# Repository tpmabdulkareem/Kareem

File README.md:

##                                          Welcome to Kareem's Fablab 
<br> 

### "_Make Almost Anything!, a brilliant creative space for budding product designers and entrepreneurs to test out their ideas and bring them to life._"

### What is fablab?

   _Fab labs provide widespread access to modern means for invention. They began as an outreach project from MIT's Center for Bits and    Atoms (CBA), and became into a collaborative and global network. You can find more information about Fab Labs on the Fab Foundation   Website. The annotated photo below illustrates the facilities of a typical Fab Lab._
   
   _A fab lab (fabrication laboratory) is a small-scale workshop offering (personal) digital fabrication. A fab lab is typically equipped with an array of flexible computer-controlled tools that cover several different length scales and various materials, with the aim to make "almost anything". This includes technology-enabled products generally perceived as limited to mass production._
   
  _While fab labs have yet to compete with mass production and its associated economies of scale in fabricating widely distributed products, they have already shown the potential to empower individuals to create smart devices for themselves. These devices can be tailored to local or personal needs in ways that are not practical or economical using mass production._
   
   _The fab lab movement is closely aligned with the DIY, the open source hardware and the free and open source movement, and shares philosophy as well as technology with them._
   
   ----

#  [ABOUT ME](https://tpmabdulkareem.github.io/About)  (Click here) 
   
-----

# _Course Progress_

##   _SYLLABUS & CONTENTS_

  Day 1 : [Introduction To Fablab](https://tpmabdulkareem.github.io/Day1)

  Day 2 : [Github Pages and Documentation](https://tpmabdulkareem.github.io/Day2)
                               
  Day 3 : [Laser Cutting,Moulding and Casting](https://tpmabdulkareem.github.io/Day3)
                                
  Day 4 : [Vinyl Cutting](https://tpmabdulkareem.github.io/Day4)
                                	
  Day 5 : [Screen Printing](https://tpmabdulkareem.github.io/Day5)
                                	
  Day 6 : [3D Printing](https://tpmabdulkareem.github.io/Day6)
                                
  Day 7 : [Electronics Production and CNC](https://tpmabdulkareem.github.io/Day7)
  
  ----
                                
##   [Projects](https://tpmabdulkareem.github.io/project)
 
 -----

## [Gallery](https://tpmabdulkareem.github.io/gallery)

 -----

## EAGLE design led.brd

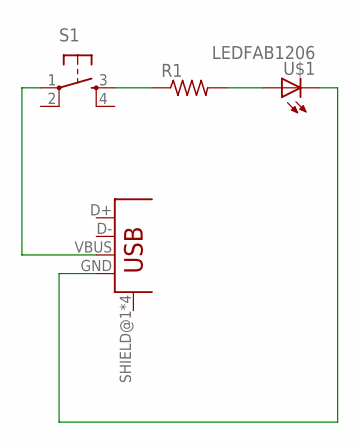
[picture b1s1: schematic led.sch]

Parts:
R1: RES-US1206FAB; R1206FAB
S1: 6MM_SWITCH6MM_SWITCH; 6MM_SWITCH
U$1: LEDFAB1206; LED1206FAB
U$2: USB_MINIB

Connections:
unnamed: S1.1, U$2.VBUS
unnamed: R1.1, S1.3 (S)
unnamed: R1.2, U$1.1 (A)
unnamed: U$1.2 (C), U$2.GND

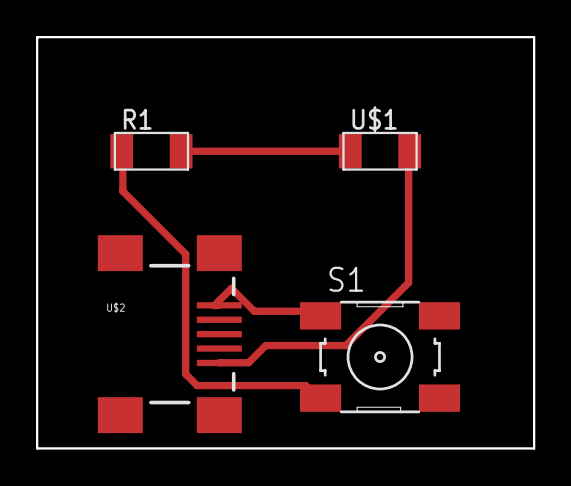
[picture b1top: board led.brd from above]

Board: 2 copper layers, 27.6 x 22.9 mm, 4 parts (0 on the bottom side), 4 nets.

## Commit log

2017-08-23 Set theme jekyll-theme-midnight
2017-08-24 Create About me
2017-08-24 Set theme jekyll-theme-hacker
2017-08-24 Rename About me.md to About.md
2017-08-24 Create DAY1
2017-09-03 Set theme jekyll-theme-leap-day
2017-09-03 Set theme jekyll-theme-dinky
2017-09-03 Set theme jekyll-theme-slate
2017-09-03 Create day2
2017-09-03 Rename DAY1 to Day1
2017-09-03 Rename day2 to Day2
2017-09-03 Create gallery
2017-09-03 Rename Day1 to Day1.md
2017-09-05 Set theme jekyll-theme-cayman
2017-09-06 Create Day6
2017-09-06 Update Day6
2017-09-06 Rename Day6 to Day6.md
2017-09-07 Create 3D
2017-09-07 Rename 3D to 3D.md
